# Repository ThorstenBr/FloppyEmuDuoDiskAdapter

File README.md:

# FloppyEmu DuoDisk Adapter
This project contains a KiCad PCB to create a FloppyEmu-DuoDisk Adapter for the [Big Mess of Wires - FloppyEmu](https://www.bigmessowires.com/floppy-emu/) - an SD-card based disk drive emulator for the Apple II computer.
The adapter allows to connect the FloppyEmu to the DuoDisk cable and switch each drive separately (select each of the two DuoDisk drives or each of the two emulated FloppyEmu drives).

This adapter is for the Apple II DuoDisk only. It will not work with the Disk II drive. You can buy a switch adapter for the Disk II drive directly from [Big Mess of Wires](https://shop.bigmessowires.com/products/apple-disk-drive-ab-switch).

## License
This project is released under the "Creative Commons Attribution 4.0 International Public License". See [LICENSE](/LICENSE).

## Description
The adapter plugs into the DuoDisk's rear DB-25 connector - and provides a DB-25 connector for the DuoDisk cable from the Apple II disk interface card.
The card also provides a standard box header to connect the FloppyEmu ribbon cable:

There are three switches on the adapter:

* **DRIVE1**: maps the Apple II drive 1 to either the DuoDisk or the FloppyEmu.
* **DRIVE2**: maps the Apple II drive 2 to either the DuoDisk or the FloppyEmu.
* **SWAP 1/2**: swaps the FloppyEmu drives 1+2. This switch is not strictly needed (can be replaced by soldered jumpers). However, I found it convenient when running a mixed setup, with one drive mapped to the DuoDisk and one to the FloppyEmu. So you could map drive 1 (boot drive) to the DuoDisk, and map the drive 2 to FloppyEmu - but then swap the FloppyEmu drives, so drive 2 is actually mapped to FloppyEmu drive 1 (the default drive) instead.

## Parts List
Parts list for the completed PCB:
* 1x 2x10pin box header
* 1x DB-25 male connector
* 1x DB-25 female connector
* 1x 470 Ohm resistor
* 4x 10K Ohm resistor
* 2x Toggle Switch ON/ON (cheap Goobay KNX-1)
* optional: 1x Toggle Switch 2xON/ON (cheap Goobay KNX-2)

I ordered parts from my usual German electronics online shop for about 4€. I created a public shopping list containing all the parts.
Parts are very common and should remain available. I'd expect that only the two switches may depend upon availability - but there are many similar switches, so these are easily replaced.

[Shopping List at Reichelt.de](https://www.reichelt.de/my/1958081?LANGUAGE=EN):
* 1x WSL 20G
* 1x D-SUB ST 25
* 1x D-SUB BU 25
* 1x 1/4W 470
* 4x 1/4W 10K
* 2x GOOBAY 10020
* 1x GOOBAY 10021

## Gerber Files, Ordering a PCB
If you wished to directly order a PCB (PCBWay, JLCPCB etc) you could use the latest Gerber files from the [Gerber](/Gerber/) directory. Just upload the ZIP file to your preferred PCB manufacturer and order the PCB. My PCBs were manufactured by JLCPCB (using the cheapest options, I got mine already after about 1.5 weeks for a few bucks/Euros).

## Soldering
Soldering is straight forward. Only simple through-hole components are used. All part numbers and component values are marked directly on the PCB.

Just take care to not mix up the male and female DB-25 connectors. Having to desolder these is messy - you do not want the experience... :)
* Solder the female DB-25 connector to J1 (Apple II Drive Controller).
* Solder the male DB-25 connector to J2 (DuoDisk).

The DB-25 connectors for J1/J2 use simple "solder bucket" pins (not straight, nor angled pins).
The PCB is simply plugged in between the two bucket rows - and then soldered. It's easy - and indeed a very rigid connection.

**DOUBLE-CHECK THE PROPER ORIENTATION OF THE BOX HEADER!**  
The notch for the box header is clearly marked on the PCB. The notch must be facing towards the J2/DuoDisk-side of the PCB.
Incorrect orientation of the box header for FloppyEmu could damage or destroy your FloppyEmu, Apple II - or both...

### Soldering Options
The toggle switch to SWAP drive 1+2 of FloppyEmu is optional. You may find it convenient when mixing drives of DuoDisk and FloppyEmu.
Otherwise, if you mainly plan to either use DuoDisk, or otherwise FloppyEmu, but rarely a combination, then the additional switch may just add confusion.
You can omit the "swapping switch" (SW3) and just solder jumpers instead - as shown:

Also, if you just wanted an adapter to map a single drive only (i.e. keep drive 2 fixed to DuoDisk or FloppyEmu, while only drive 1 can be switched), you can also replace switch SW2 with a soldered jumper - as shown:
* Red jumper to map disk 2 always to DuoDisk.
* Blue jumper to map disk 2 always to FloppyEmu.

Note, SW2 to switch drive 2 only makes sense for newer FloppyEmus (rev C or newer), which support dual disk emulation.
If you are using an older FloppyEmu Model B, supporting single disk emulation only, then omit switch SW2 and solder the red jumper as shown above.

## Installation
Make sure the Apple II is switched off.

**DO NOT CONNECT THE ADAPTER OR THE FLOPPY EMU WHILE YOUR MACHINE IS POWERED!**

* Disconnect the DB-25 cable from the DuoDisk.
* Instead of the DB-25 cable, plug the completed PCB into the rear of the DuoDisk.
* Connect the DB-25 cable to the adapter.
* Finally connect FloppyEmu's ribbon cable to the adapter.

The adapter will be conveniently placed just above the Apple II's main power switch. You will be used to "hug" your Apple II with your left arm, when swiching it on/off. In the same way you can now reach the switches, to chose between DuoDisk and FloppyEmu drives.

I was a initially concerned that I might have to shorten FloppyEmu's ribbon cable, since the long cable is now in series with the original DuoDisk cable. However, so far, I have not experienced any issues (reading/writing FloppyEmu disks) and I just kept the ribbon cable at its original length.

## Usage
* The middle switch (SW1) maps Disk 1 to DuoDisk when the switch is flipped to the rear, otherwise Disk 1 of FloppyEmu is enabled.
* The front switch (SW2) maps Disk 2 to DuoDisk when the switch is flipped to the rear, otherwise Disk 2 of FloppyEmu is enabled.
* SW3, if installed, allows to swap Disks 1/2 of Floppy Emu. Default setting is when SW3 is flipped to the front (Disk 1/2=FloppyEmu Disk 1/2), otherwise the drives are swapped.

In most cases you can flip the middle switch only (toggle drive 1 between DuoDisk and FloppyEmu). The other switches are only relevant when you plan to use multiple drives, e.g. to copy data from a real disk to FloppyEmu or vice versa.

Do not flip the switches while the drives are actively used. This could result in corrupted disks, when writing.
It's safe to flip the switches, however, while the drives are not being accessed.

### Copying Disks
You can copy between real disks in your DuoDisk drive and emulated FloppyEmu disks.
Carefully read the FloppyEmu manual on copying disks: while there are no limitations when copying from an emulated to a real disk, there are limitations when copying entire disks to FloppyEmu (i.e. the emulation does not supported formatting, .woz disk format should be used - see [FloppyEmu manual](http://www.bigmessowires.com/femu-instructions.pdf) for details).

## Schematics and KiCad Project
The [KiCad](/KiCad/) folder contains the schematics and PCB project files, if you wished to adapt the design.

## Trivia
*Q: What about the tiny PCB imprint below the swap 1/2 switch?*  
*A: Only users of an Apple II with German character set will understand...* :-)

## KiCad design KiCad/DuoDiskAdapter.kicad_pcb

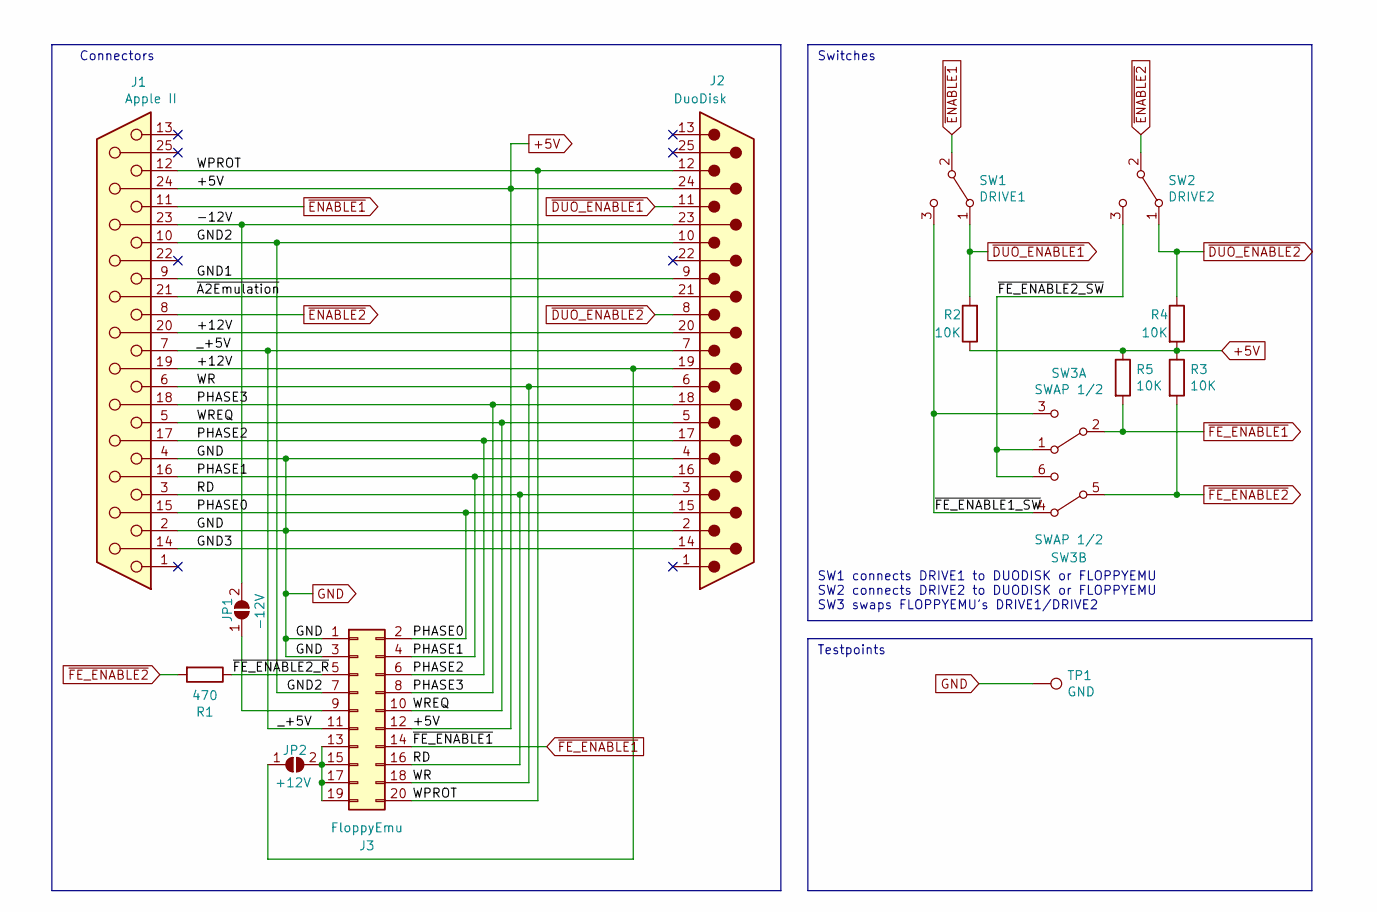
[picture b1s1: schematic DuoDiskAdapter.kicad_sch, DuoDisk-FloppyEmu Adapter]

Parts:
J1: Apple II; DSUB-25_Female_EdgeMount_Pitch2.77mm
J2: DuoDisk; DSUB-25_Male_EdgeMount_Pitch2.77mm
J3: FloppyEmu; Header_2x10_Shrouded_100mil
JP1: -12V; SolderJumper-2_P1.3mm_Open_RoundedPad1.0x1.5mm
JP2: +12V; SolderJumper-2_P1.3mm_Open_RoundedPad1.0x1.5mm
R1: 470; R_Axial_DIN0207_L6.3mm_D2.5mm_P10.16mm_Horizontal
R2, R3, R4, R5: 10K; R_Axial_DIN0207_L6.3mm_D2.5mm_P10.16mm_Horizontal
SW1: DRIVE1; KNX-1
SW2: DRIVE2; KNX-1
SW3: SWAP 1/2; KNX-2
TP1: GND; Measurement_Point_Round-TH_Small

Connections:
+5V: J1.24, J2.24, J3.12, R2.1, R3.1, R4.2, R5.1
/+12V: J1.19, J1.20, J2.19, J2.20, JP2.1 (A)
/-12V: J1.23, J2.23, JP1.2 (B)
/GND1: J1.9, J2.9
/GND2: J1.10, J2.10, J3.7
/GND3: J1.14, J2.14
/PHASE0: J1.15, J2.15, J3.2
/PHASE1: J1.16, J2.16, J3.4
/PHASE2: J1.17, J2.17, J3.6
/PHASE3: J1.18, J2.18, J3.8
/RD: J1.3, J2.3, J3.16
/WPROT: J1.12, J2.12, J3.20
/WR: J1.6, J2.6, J3.18
/WREQ: J1.5, J2.5, J3.10
/_+5V: J1.7, J2.7, J3.11
/~A2Emulation: J1.21, J2.21
/~FE_ENABLE1_SW: SW1.3 (C), SW3.3 (C), SW3.4 (A)
/~FE_ENABLE2_R: J3.5, R1.1
/~FE_ENABLE2_SW: SW2.3 (C), SW3.1 (A), SW3.6 (C)
GND: J1.2, J1.4, J2.2, J2.4, J3.1, J3.3, TP1.1
unnamed: J3.9, JP1.1 (A)
unnamed: J3.13, J3.15, J3.17, J3.19, JP2.2 (B)
~DUO_ENABLE1: J2.11, R2.2, SW1.1 (A)
~DUO_ENABLE2: J2.8, R4.1, SW2.1 (A)
~ENABLE1: J1.11, SW1.2 (B)
~ENABLE2: J1.8, SW2.2 (B)
~FE_ENABLE1: J3.14, R5.2, SW3.2 (B)
~FE_ENABLE2: R1.2, R3.2, SW3.5 (B)

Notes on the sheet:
SW1 connects DRIVE1 to DUODISK or FLOPPYEMU SW2 connects DRIVE2 to DUODISK or FLOPPYEMU SW3 swaps FLOPPYEMU's DRIVE1/DRIVE2
Testpoints
Connectors
Switches

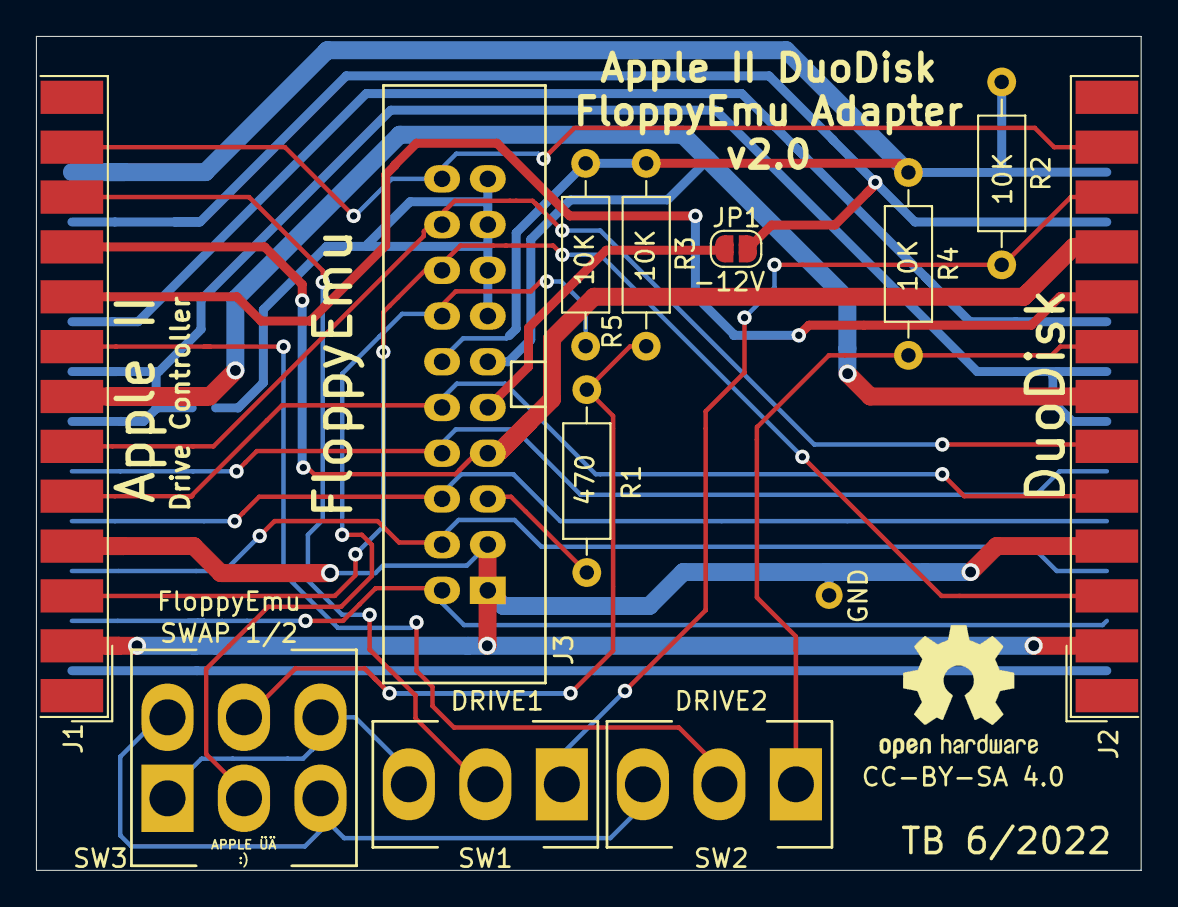
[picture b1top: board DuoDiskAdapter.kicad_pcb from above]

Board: 2 copper layers, 61.4 x 46.3 mm, 14 parts (1 on the bottom side), 28 nets.

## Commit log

2022-06-13 Initial commit.
2022-06-13 Added license and readme.
2022-06-14 Update LICENSE
    CC-BY-SA license
2022-06-14 Updated PCB and Gerber files.
2022-06-21 v1.1: fixed FloppyEmu connector: Added extra +5V connection to pin 11.
2022-06-21 Changed pull-ups to 10K. 10K is enough and reduces load (especially since the disk drive itself usually also has a pull-up).
2022-06-21 Updated README. Added photos of completed PCB.
2022-06-21 Added installation description. Added photo showing installation.
2022-06-21 Updated README Added shopping list. Moved Gerber directory to top-level.
2022-06-22 Improved README.
2022-10-25 Updated KiCad design files to reflect correct pin name for D-SUB/pin21. D-SUB/pin 21 is actually not a ground pin, but the "/Apple II emulation" pin. It is just hard-wired to GND by the AppleII cable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
2022-12-21 v2.0: added solder jumpers for +/-12V These are not required for FloppyEmu (should be left open). Closing the jumpers provides the option to connect real Disk II drives.

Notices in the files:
KiCad/DuoDiskAdapter.kicad_pcb:
CC-BY-SA 4.0
